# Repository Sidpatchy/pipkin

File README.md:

# Pipkin
A 2.4GHz LoRa radio based on the XIAO nRF54L15 and the EBYTE E28-2G4M27SX. REV.A is fully validated and known to work on a hardware level.

More images can be found in [/assets/](https://github.com/Sidpatchy/pipkin/tree/main/assets)

## Hardware diagnostic firmware
See [`test_firmware`](test_firmware) for the PlatformIO project used to test
SX1281 SPI communication and scan the external I2C connector.

## XIAO nRF52840
While untested, the radio will still theoretically work with a XIAO nRF52840. I2C and DI02/DI03 are lost with the nRF52 board as it lacks extra GPIO underneath. The battery + and - terminals on the XIAO or Pipkin board should be masked to prevent shorts if an nRF52840 board is used.

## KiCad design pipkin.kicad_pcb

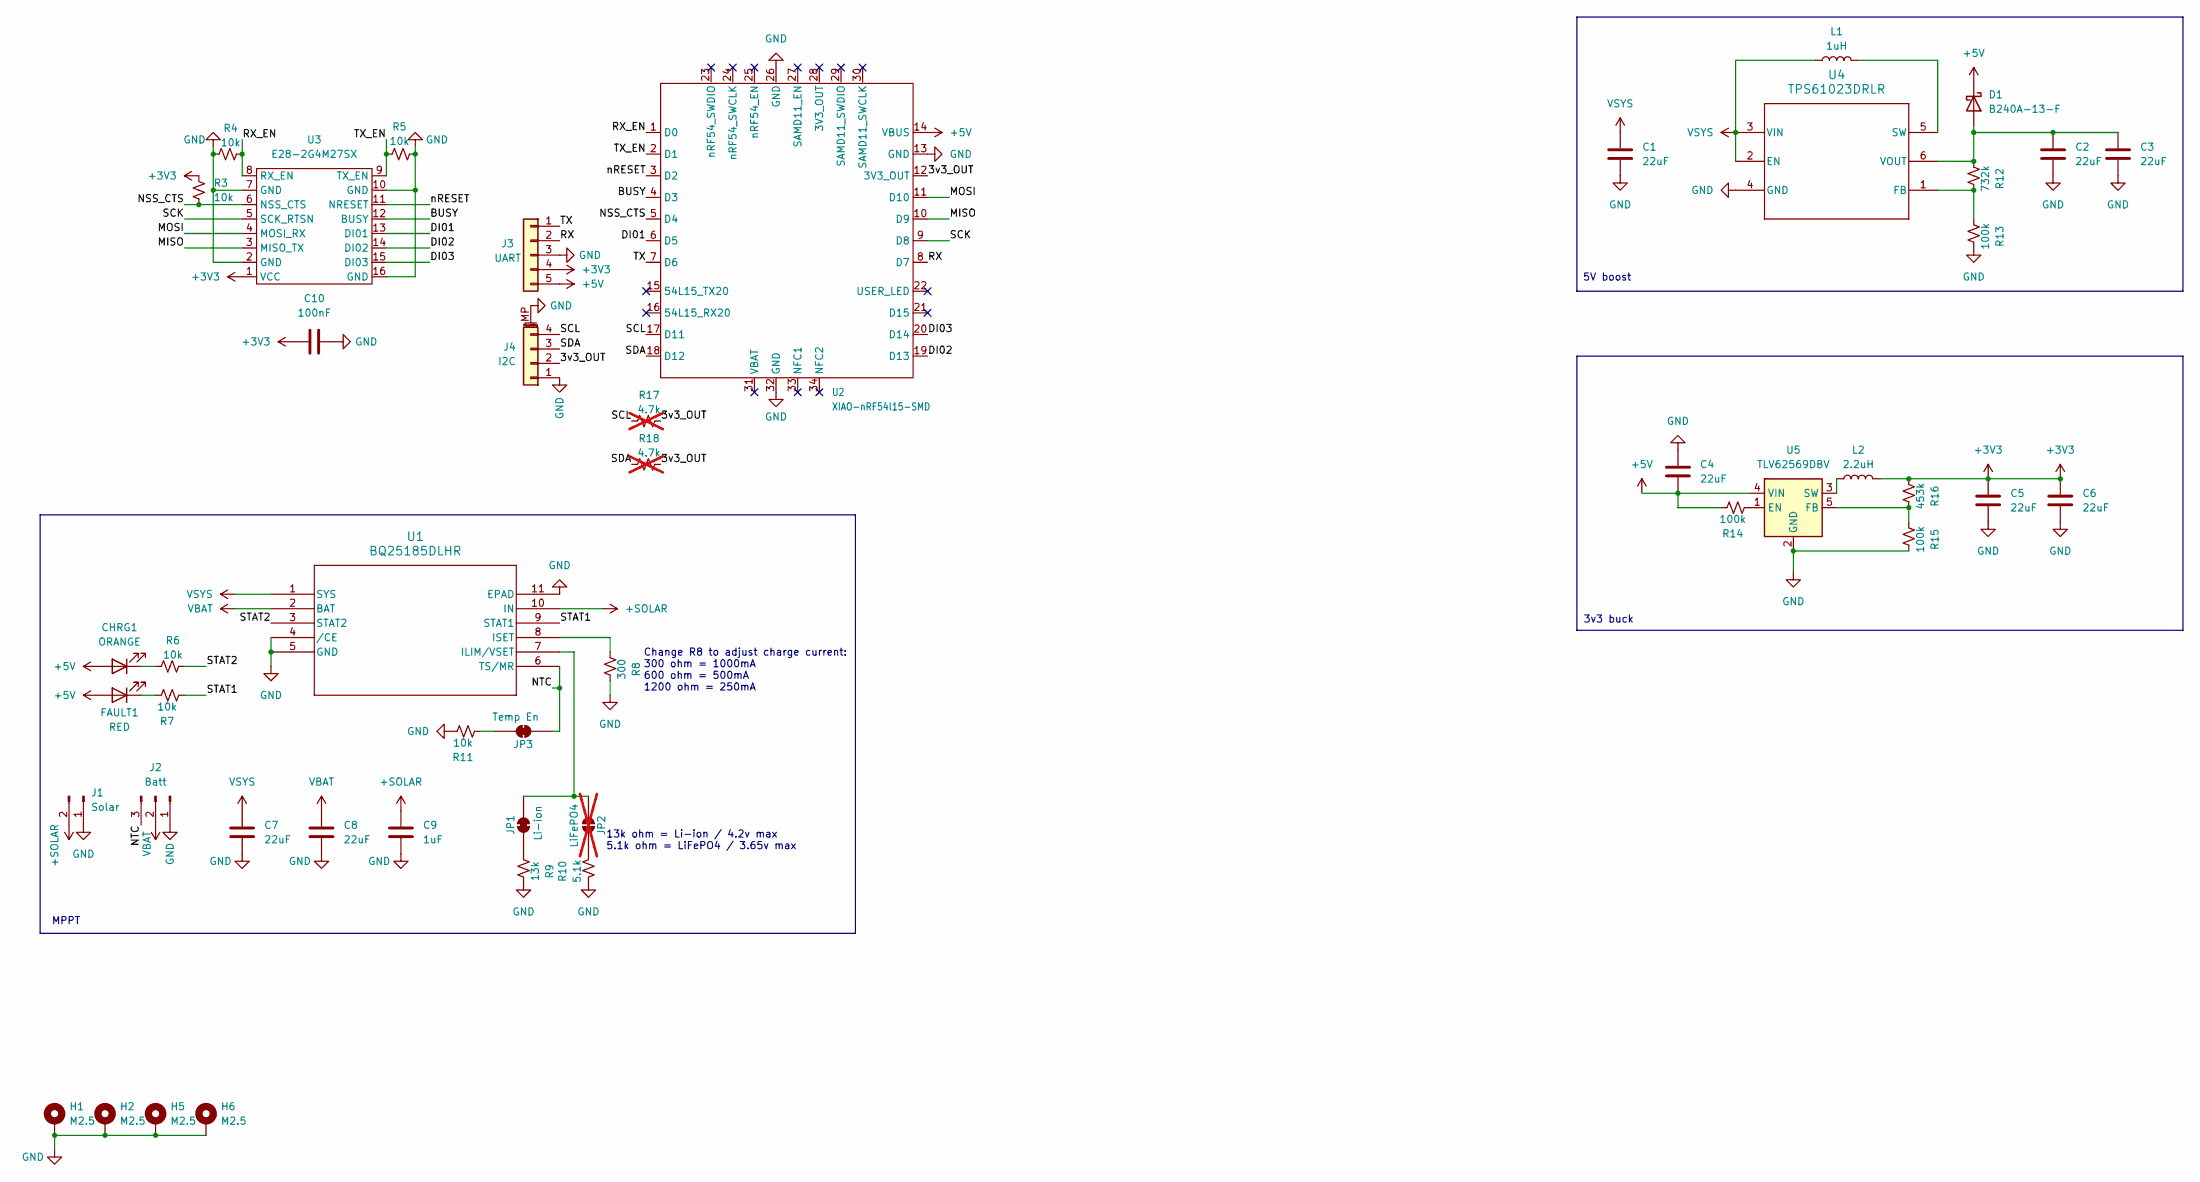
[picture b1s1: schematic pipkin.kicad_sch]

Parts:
C1, C2, C3, C4, C5, C6, C7, C8: 22uF; C_0805_2012Metric
C9: 1uF; C_0805_2012Metric
C10: 100nF; C_0603_1608Metric
CHRG1: ORANGE; LED_0603_1608Metric
D1: B240A-13-F; D_SMA
FAULT1: RED; LED_0603_1608Metric
H1, H2, H5, H6: M2.5; MountingHole_2.7mm_M2.5_DIN965_Pad
J1: Solar; JST_PH_B2B-PH-K_1x02_P2.00mm_Vertical
J2: Batt; JST_PH_B3B-PH-K_1x03_P2.00mm_Vertical
J3: UART; PinHeader_1x05_P2.54mm_Vertical
J4: I2C; JST_SH_BM04B-SRSS-TB_1x04-1MP_P1.00mm_Vertical
JP1: Li-ion; R_0402_1005Metric
JP2: LiFePO4; R_0402_1005Metric; not fitted
JP3: Temp En; R_0402_1005Metric
L1: 1uH; L_Wuerth_MAPI-4020
L2: 2.2uH; L_Wuerth_MAPI-4020
R3, R4, R5, R6, R7, R11: 10k; R_0402_1005Metric
R8: 300; R_0402_1005Metric
R9: 13k; R_0402_1005Metric
R10: 5.1k; R_0402_1005Metric
R12: 732k; R_0402_1005Metric
R13, R14, R15: 100k; R_0402_1005Metric
R16: 453k; R_0402_1005Metric
R17, R18: 4.7k; R_0402_1005Metric; not fitted
U1: BQ25185DLHR; WSON10_DLH_TEX
U2: XIAO-nRF54l15-SMD
U3: E28-2G4M27SX; E28
U4: TPS61023DRLR; DRL0006A
U5: TLV62569DBV; SOT-23-5

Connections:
+3V3: C5.2, C6.2, C10.1, J3.4, L2.2, R3.2, R16.2, U3.1 (VCC)
+5V: C4.1, CHRG1.2 (A), D1.1 (K), FAULT1.2 (A), J3.5, R14.1, U2.14 (VBUS), U5.4 (VIN)
+SOLAR: C9.1, J1.2, U1.10 (IN)
/3v3_OUT: J4.2, R17.1, R18.1, U2.12 (3V3_OUT)
/BUSY: U2.4 (D3), U3.12 (BUSY)
/DI01: U2.6 (D5), U3.13 (DI01)
/DI02: U2.19 (D13), U3.14 (DI02)
/DI03: U2.20 (D14), U3.15 (DI03)
/MISO: U2.10 (D9), U3.3 (MISO_TX)
/MOSI: U2.11 (D10), U3.4 (MOSI_RX)
/NSS_CTS: R3.1, U2.5 (D4), U3.6 (NSS_CTS)
/NTC: J2.3, JP3.2 (B), U1.6 (TS/MR)
/RX: J3.2, U2.8 (D7)
/RX_EN: R4.1, U2.1 (D0), U3.8 (RX_EN)
/SCK: U2.9 (D8), U3.5 (SCK_RTSN)
/SCL: J4.4, R17.2, U2.17 (D11)
/SDA: J4.3, R18.2, U2.18 (D12)
/STAT1: R7.2, U1.9 (STAT1)
/STAT2: R6.1, U1.3 (STAT2)
/TX: J3.1, U2.7 (D6)
/TX_EN: R5.2, U2.2 (D1), U3.9 (TX_EN)
/nRESET: U2.3 (D2), U3.11 (NRESET)
GND: C1.2, C2.2, C3.2, C4.2, C5.1, C6.1, C7.2, C8.2, C9.2, C10.2, H1.1 (1_1), H2.1 (1_1), H5.1 (1_1), H6.1 (1_1), J1.1, J2.1, J3.3, J4.1, J4.MP (MountPin), R4.2, R5.1, R8.1, R9.1, R10.1, R11.1, R13.1, R15.1, U1.4 (/CE), U1.5 (GND), U1.11 (EPAD), U2.13 (GND), U2.26 (GND), U2.32 (GND), U3.2 (GND), U3.7 (GND), U3.10 (GND), U3.16 (GND), U4.4 (GND), U5.2 (GND)
unnamed: CHRG1.1 (K), R6.2
unnamed: C2.1, C3.1, D1.2 (A), R12.2, U4.6 (VOUT)
unnamed: FAULT1.1 (K), R7.1
unnamed: JP1.1 (A), JP2.2 (B), U1.7 (ILIM/VSET)
unnamed: JP1.2 (B), R9.2
unnamed: JP2.1 (A), R10.2
unnamed: JP3.1 (A), R11.2
unnamed: R8.2, U1.8 (ISET)
unnamed: R12.1, R13.2, U4.1 (FB)
unnamed: L1.2, U4.5 (SW)
unnamed: R14.2, U5.1 (EN)
unnamed: R15.2, R16.1, U5.5 (FB)
unnamed: L2.1, U5.3 (SW)
VBAT: C8.1, J2.2, U1.2 (BAT)
VSYS: C1.1, C7.1, L1.1, U1.1 (SYS), U4.2 (EN), U4.3 (VIN)

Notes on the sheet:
5V boost
13k ohm = Li-ion / 4.2v max 5.1k ohm = LiFePO4 / 3.65v max
3v3 buck
Change R8 to adjust charge current: 300 ohm = 1000mA 600 ohm = 500mA 1200 ohm = 250mA
MPPT

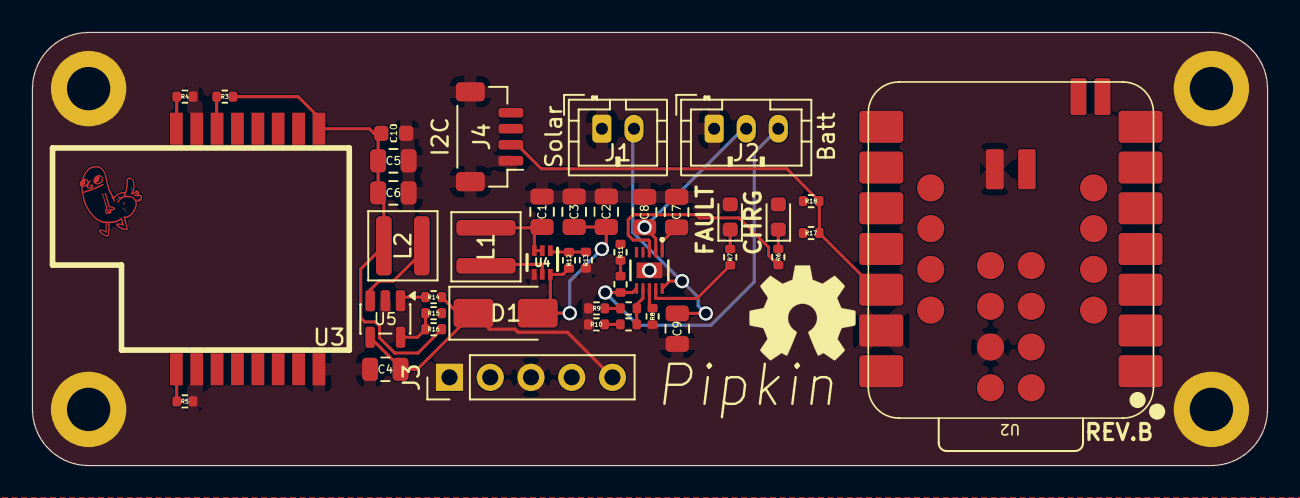
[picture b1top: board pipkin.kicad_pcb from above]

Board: 2 copper layers, 77.0 x 27.0 mm, 47 parts (0 on the bottom side), 38 nets.

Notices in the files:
pipkin.kicad_pcb:
CERN-OHL-S-2.0
© 2026 Sidpatchy
